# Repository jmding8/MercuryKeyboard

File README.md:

# Mercury

Mercury is a row staggered keyboard with 42 keys that kind of looks like a pair of wings. It is primarily designed as a split, wireless, low-profile keyboard. Other build configurations are also possible, but full feature parity is not guaranteed. If you are looking for a 40% keyboard with thumb keys and a conventional row staggered layout, then Mercury might be for you.

With MBK keycaps, Mercury is 19mm thick from table to typing-surface. Its batteries are fully enclosed and protected inside the case of the keyboard. Default firmware is pre-compiled with a keymap that I personally use exclusively and on a daily basis.

## Resources
1. [Bill of materials](/text/bill_of_materials.md)
1. [Build guide](/text/build_guide.md)
1. [Manufacturing notes](/text/manufacturing_notes.md)
1. [Firmware and keymap notes](/text/firmware_notes.md)

## Alternative Configurations

* MX-style, full-height switches
* USB wired
* Monoblock, aka non-split

1. Split, wired, full-height

1. Monoblock, wireless, low-profile

1. Monoblock, wired, low-profile

## To-Do

1. Upload ZMK source.
2. Merge shield into ZMK main.

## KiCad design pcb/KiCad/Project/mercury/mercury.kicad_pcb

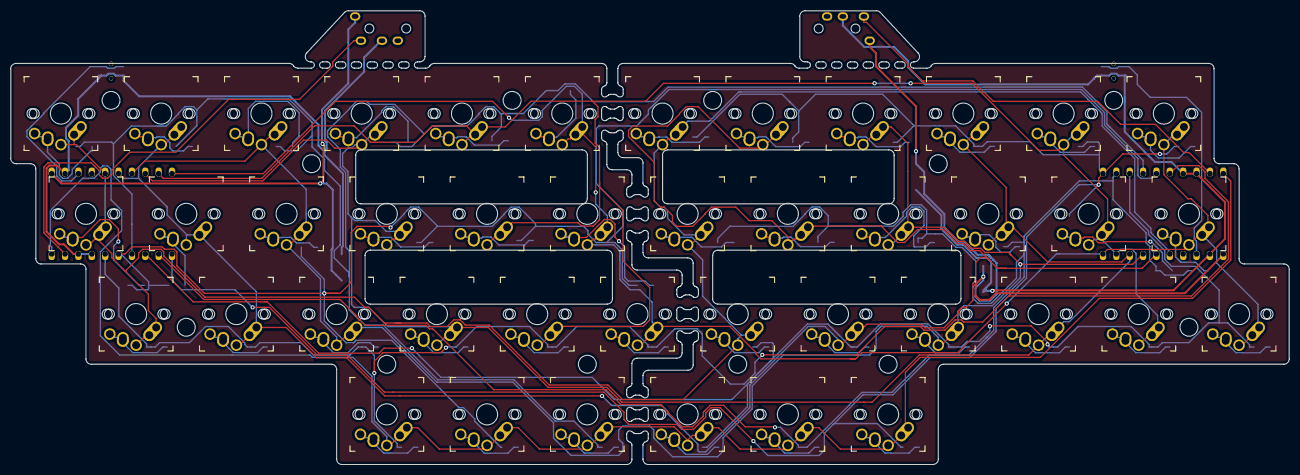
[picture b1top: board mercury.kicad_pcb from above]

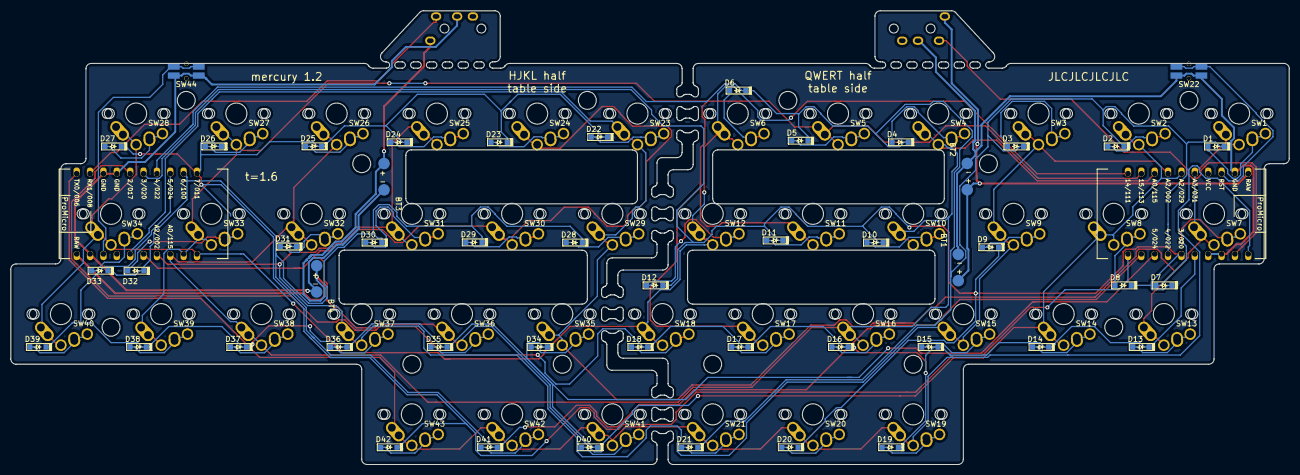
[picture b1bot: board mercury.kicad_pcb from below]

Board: 2 copper layers, 242.9 x 86.2 mm, 94 parts (48 on the bottom side), 63 nets.

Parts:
BT1, BT2, BT3, BT4: Battery_Cell; Battery-TH
D1, D2, D3, D4, D5, D6, D7, D8, D9, D10, D11, D12, D13, D14, D15, D16, D17, D18, D19, D20, D21, D22, D23, D24, D25, D26, D27, D28, D29, D30, D31, D32, D33, D34, D35, D36, D37, D38, D39, D40, D41, D42: D; D_SOD123
J1, J2: AudioJack4; TRRS-PJ-320A
SW1, SW2, SW3, SW4, SW5, SW6, SW7, SW8, SW9, SW10, SW11, SW12, SW13, SW14, SW15, SW16, SW17, SW18, SW19, SW20, SW21, SW23, SW24, SW25, SW26, SW27, SW28, SW29, SW30, SW31, SW32, SW33, SW34, SW35, SW36, SW37, SW38, SW39, SW40, SW41, SW42, SW43: SW_SPST; MxAlpsChoc-Classic
SW22, SW44: SW_SPST; YD-3414
U1, U2: nice_nano; nice_nano_over_mount

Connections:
unnamed: BT1.1, BT2.1, J1.S, U1.24
unnamed: BT1.2, BT2.2, J1.R1, SW22.2, U1.3, U1.4, U1.23
unnamed: BT3.1, BT4.1, J2.S, U2.24
unnamed: BT3.2, BT4.2, J2.R1, SW44.2, U2.3, U2.4, U2.23
unnamed: D1.1, D2.1, D3.1, D4.1, D5.1, D6.1, D21.1, U1.7, U2.7
unnamed: D1.2, SW1.1
unnamed: D2.2, SW2.1
unnamed: D3.2, SW3.1
unnamed: D4.2, SW4.1
unnamed: D5.2, SW5.1
unnamed: D6.2, SW6.1
unnamed: D7.2, SW7.1
unnamed: D8.2, SW8.1
unnamed: D9.2, SW9.1
unnamed: D7.1, D8.1, D9.1, D10.1, D11.1, D12.1, D20.1, U1.6, U2.6
unnamed: D10.2, SW10.1
unnamed: D11.2, SW11.1
unnamed: D12.2, SW12.1
unnamed: D13.1, D14.1, D15.1, D16.1, D17.1, D18.1, D19.1, U1.5, U2.5
unnamed: D13.2, SW13.1
unnamed: D14.2, SW14.1
unnamed: D15.2, SW15.1
unnamed: D16.2, SW16.1
unnamed: D17.2, SW17.1
unnamed: D18.2, SW18.1
unnamed: D19.2, SW19.1
unnamed: D20.2, SW20.1
unnamed: D21.2, SW21.1
unnamed: D22.1, D23.1, D24.1, D25.1, D26.1, D27.1, D42.1, U1.10, U2.10
unnamed: D22.2, SW23.1
unnamed: D23.2, SW24.1
unnamed: D24.2, SW25.1
unnamed: D25.2, SW26.1
unnamed: D26.2, SW27.1
unnamed: D27.2, SW28.1
unnamed: D28.1, D29.1, D30.1, D31.1, D32.1, D33.1, D41.1, U1.9, U2.9
unnamed: D28.2, SW29.1
unnamed: D29.2, SW30.1
unnamed: D30.2, SW31.1
unnamed: D31.2, SW32.1
unnamed: D32.2, SW33.1
unnamed: D33.2, SW34.1
unnamed: D34.1, D35.1, D36.1, D37.1, D38.1, D39.1, D40.1, U1.8, U2.8
unnamed: D34.2, SW35.1
unnamed: D35.2, SW36.1
unnamed: D36.2, SW37.1
unnamed: D37.2, SW38.1
unnamed: D38.2, SW39.1
unnamed: D39.2, SW40.1
unnamed: D40.2, SW41.1
unnamed: D41.2, SW42.1
unnamed: D42.2, SW43.1
unnamed: J1.T, U1.2
unnamed: J2.T, U2.2
unnamed: SW1.2, SW7.2, SW13.2, SW23.2, SW29.2, SW35.2, U1.20, U2.20
unnamed: SW4.2, SW10.2, SW16.2, SW26.2, SW32.2, SW38.2, U1.17, U2.17
unnamed: SW5.2, SW11.2, SW17.2, SW27.2, SW33.2, SW39.2, U1.16, U2.16
unnamed: SW6.2, SW12.2, SW18.2, SW28.2, SW34.2, SW40.2, U1.15, U2.15
unnamed: SW2.2, SW8.2, SW14.2, SW24.2, SW30.2, SW36.2, U1.19, U2.19
unnamed: SW3.2, SW9.2, SW15.2, SW25.2, SW31.2, SW37.2, U1.18, U2.18
unnamed: SW19.2, SW20.2, SW21.2, SW41.2, SW42.2, SW43.2, U1.1, U2.1
unnamed: SW22.1, U1.22
unnamed: SW44.1, U2.22

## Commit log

2021-08-15 initial commit, build guide and readme
2021-08-15 rename BuildGuide.md and tweak language about batteries
2021-08-15 fix typo number of mill max sockets
2021-08-15 add link readme -> build guide
2021-08-15 fix broken build guide link
2021-08-15 language tweaks
2021-09-22 add case files
2021-09-22 unify case files, update instructions and include presliced project
2021-09-24 revamp sliced case files and add print images
2021-09-24 add links to resources
2021-09-24 reword readme
2021-10-09 add firmware binaries
2021-10-09 fix typo in build guide that broke link
2021-10-09 improve flashing guide
2021-10-10 add firmwareGuide
2021-10-10 remove horizontal lines in guides
2021-10-18 Add note about flush cutters to build guide
2022-01-15 build guide: trim header pins, remove and reinstall header plastic spacer, trim switch legs, insert switches into plate before soldering
2022-01-15 build guide: clarify standoff specifications
2022-01-15 separate bill of materials, and standardize snake case
2022-01-15 single-piece -> monoblock
2022-01-15 link to print instructions from BOM
2022-01-15 tweak flush cutter language
2022-01-15 tweak readme intro
2022-07-04 add pcb files
2022-07-05 use bullets instead of numbers in manufacturing guide
2022-07-05 document alternative configurations as alternative, without full parity
2022-07-05 reference 5 files in manufacturing guide
2022-07-05 rename guides -> notes
2022-07-05 update keymap to ~3x5
2022-07-05 fix formatting for firmware notes
2022-07-05 fix keymap image, sys layer color
2022-07-05 reword intro paragraph, include reference to wings
2022-07-05 fix coloration of keymap
2022-07-06 split case files
2022-07-06 daniel2887 feedback
2025-07-03 unknown update and add source
2025-07-03 source
